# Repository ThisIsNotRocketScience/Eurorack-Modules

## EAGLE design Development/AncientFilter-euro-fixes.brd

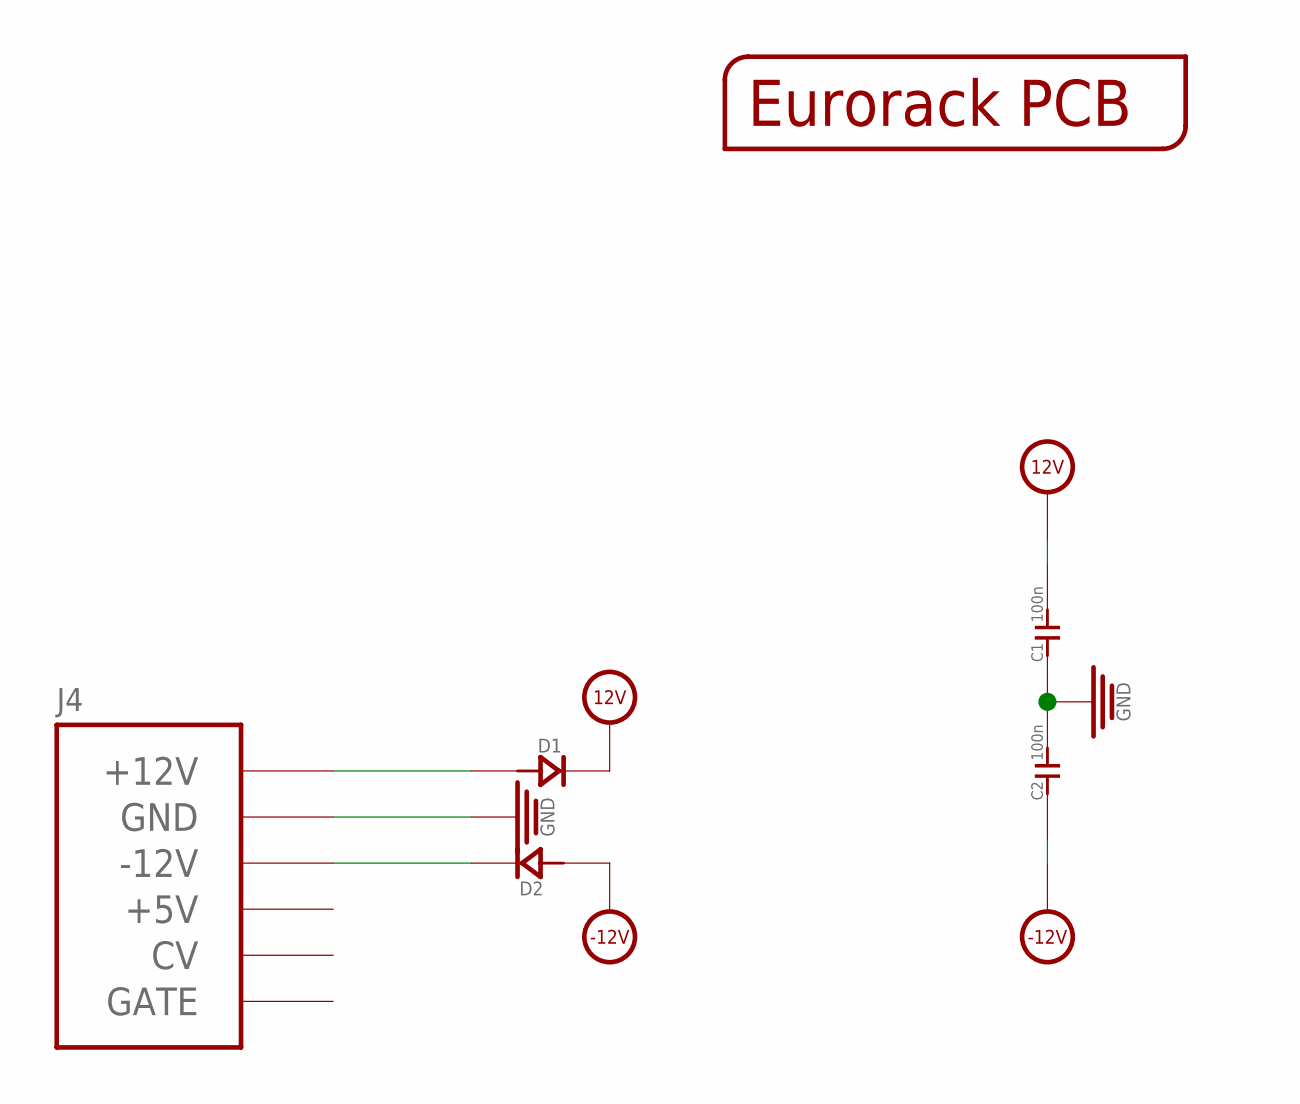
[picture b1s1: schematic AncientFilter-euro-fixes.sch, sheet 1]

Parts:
C1, C2: 100n; C0603
D1, D2: D-SMA; DO-214AC
J4: POWERSHROUDED; POWER_16_SHROUDED
PCB1: EURORACK_PCB12HP; EURORACK12HPPCB

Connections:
12V: C1.2, D1.2 (-); also elsewhere on the board
-12V: C2.1, D2.1 (+); also elsewhere on the board
GND: C1.1, C2.2, J4.3 (GND), J4.4 (GND), J4.5 (GND), J4.6 (GND), J4.7 (GND), J4.8 (GND); also elsewhere on the board
unnamed: D1.1 (+), J4.9 (+12V), J4.10 (+12V)
unnamed: D2.2 (-), J4.1 (-12V), J4.2 (-12V)

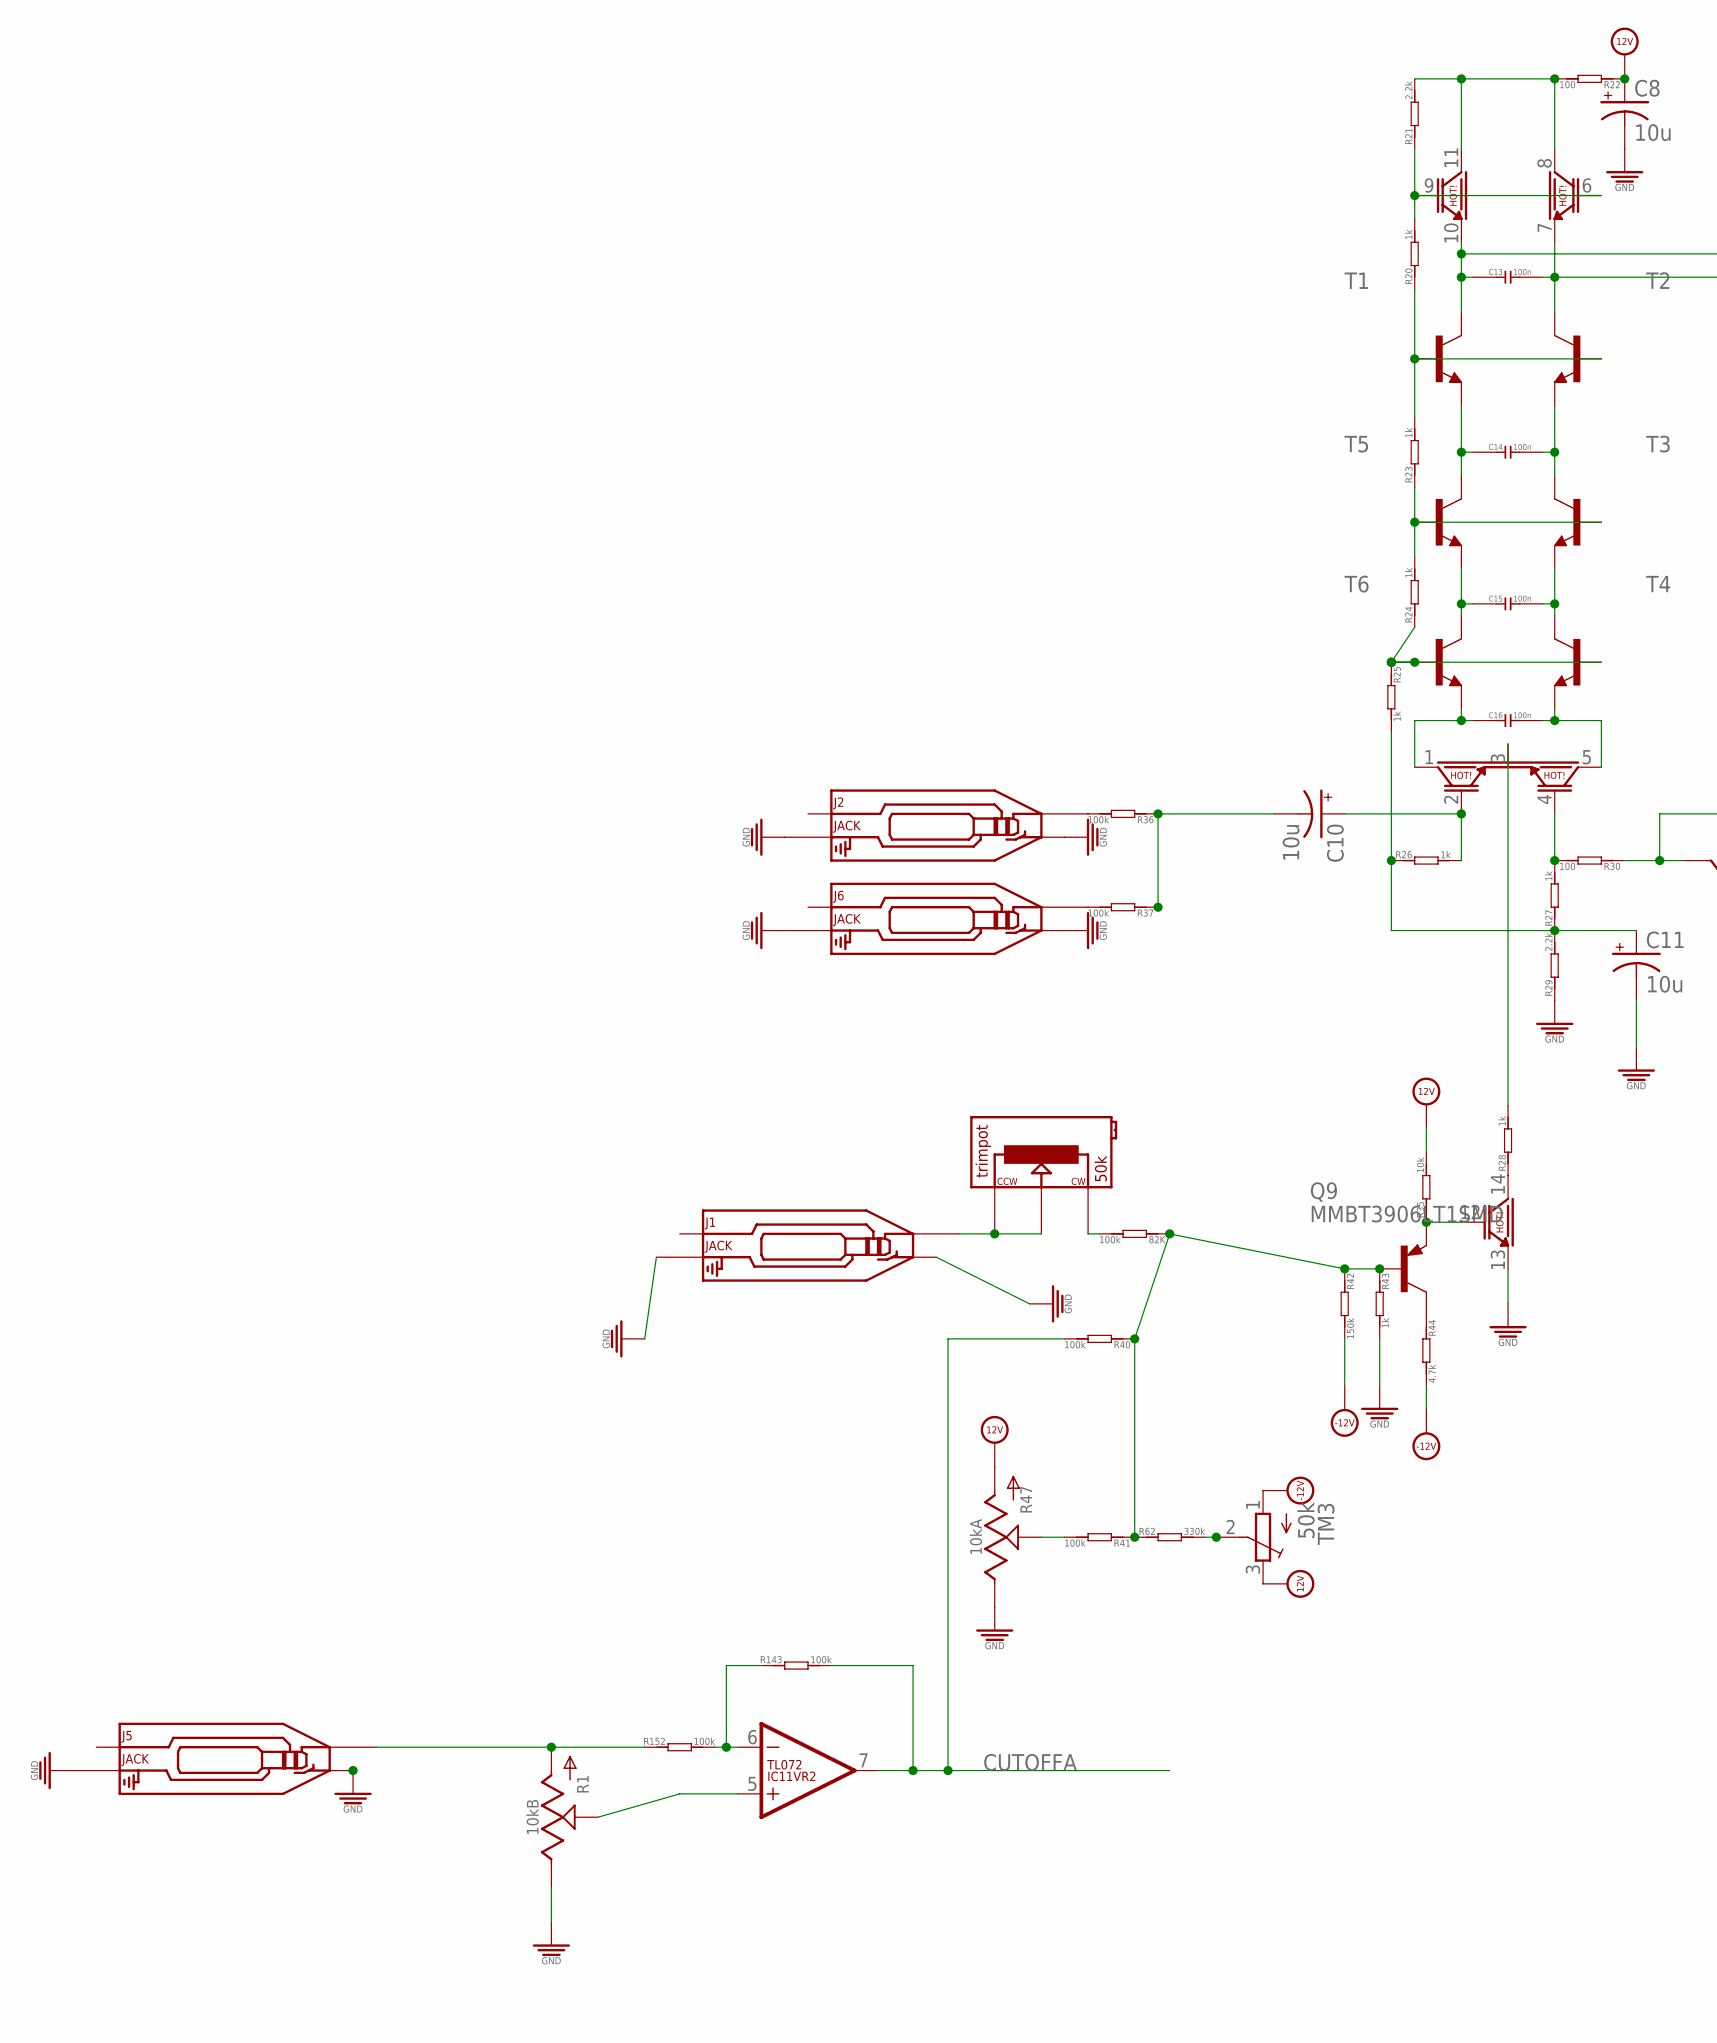
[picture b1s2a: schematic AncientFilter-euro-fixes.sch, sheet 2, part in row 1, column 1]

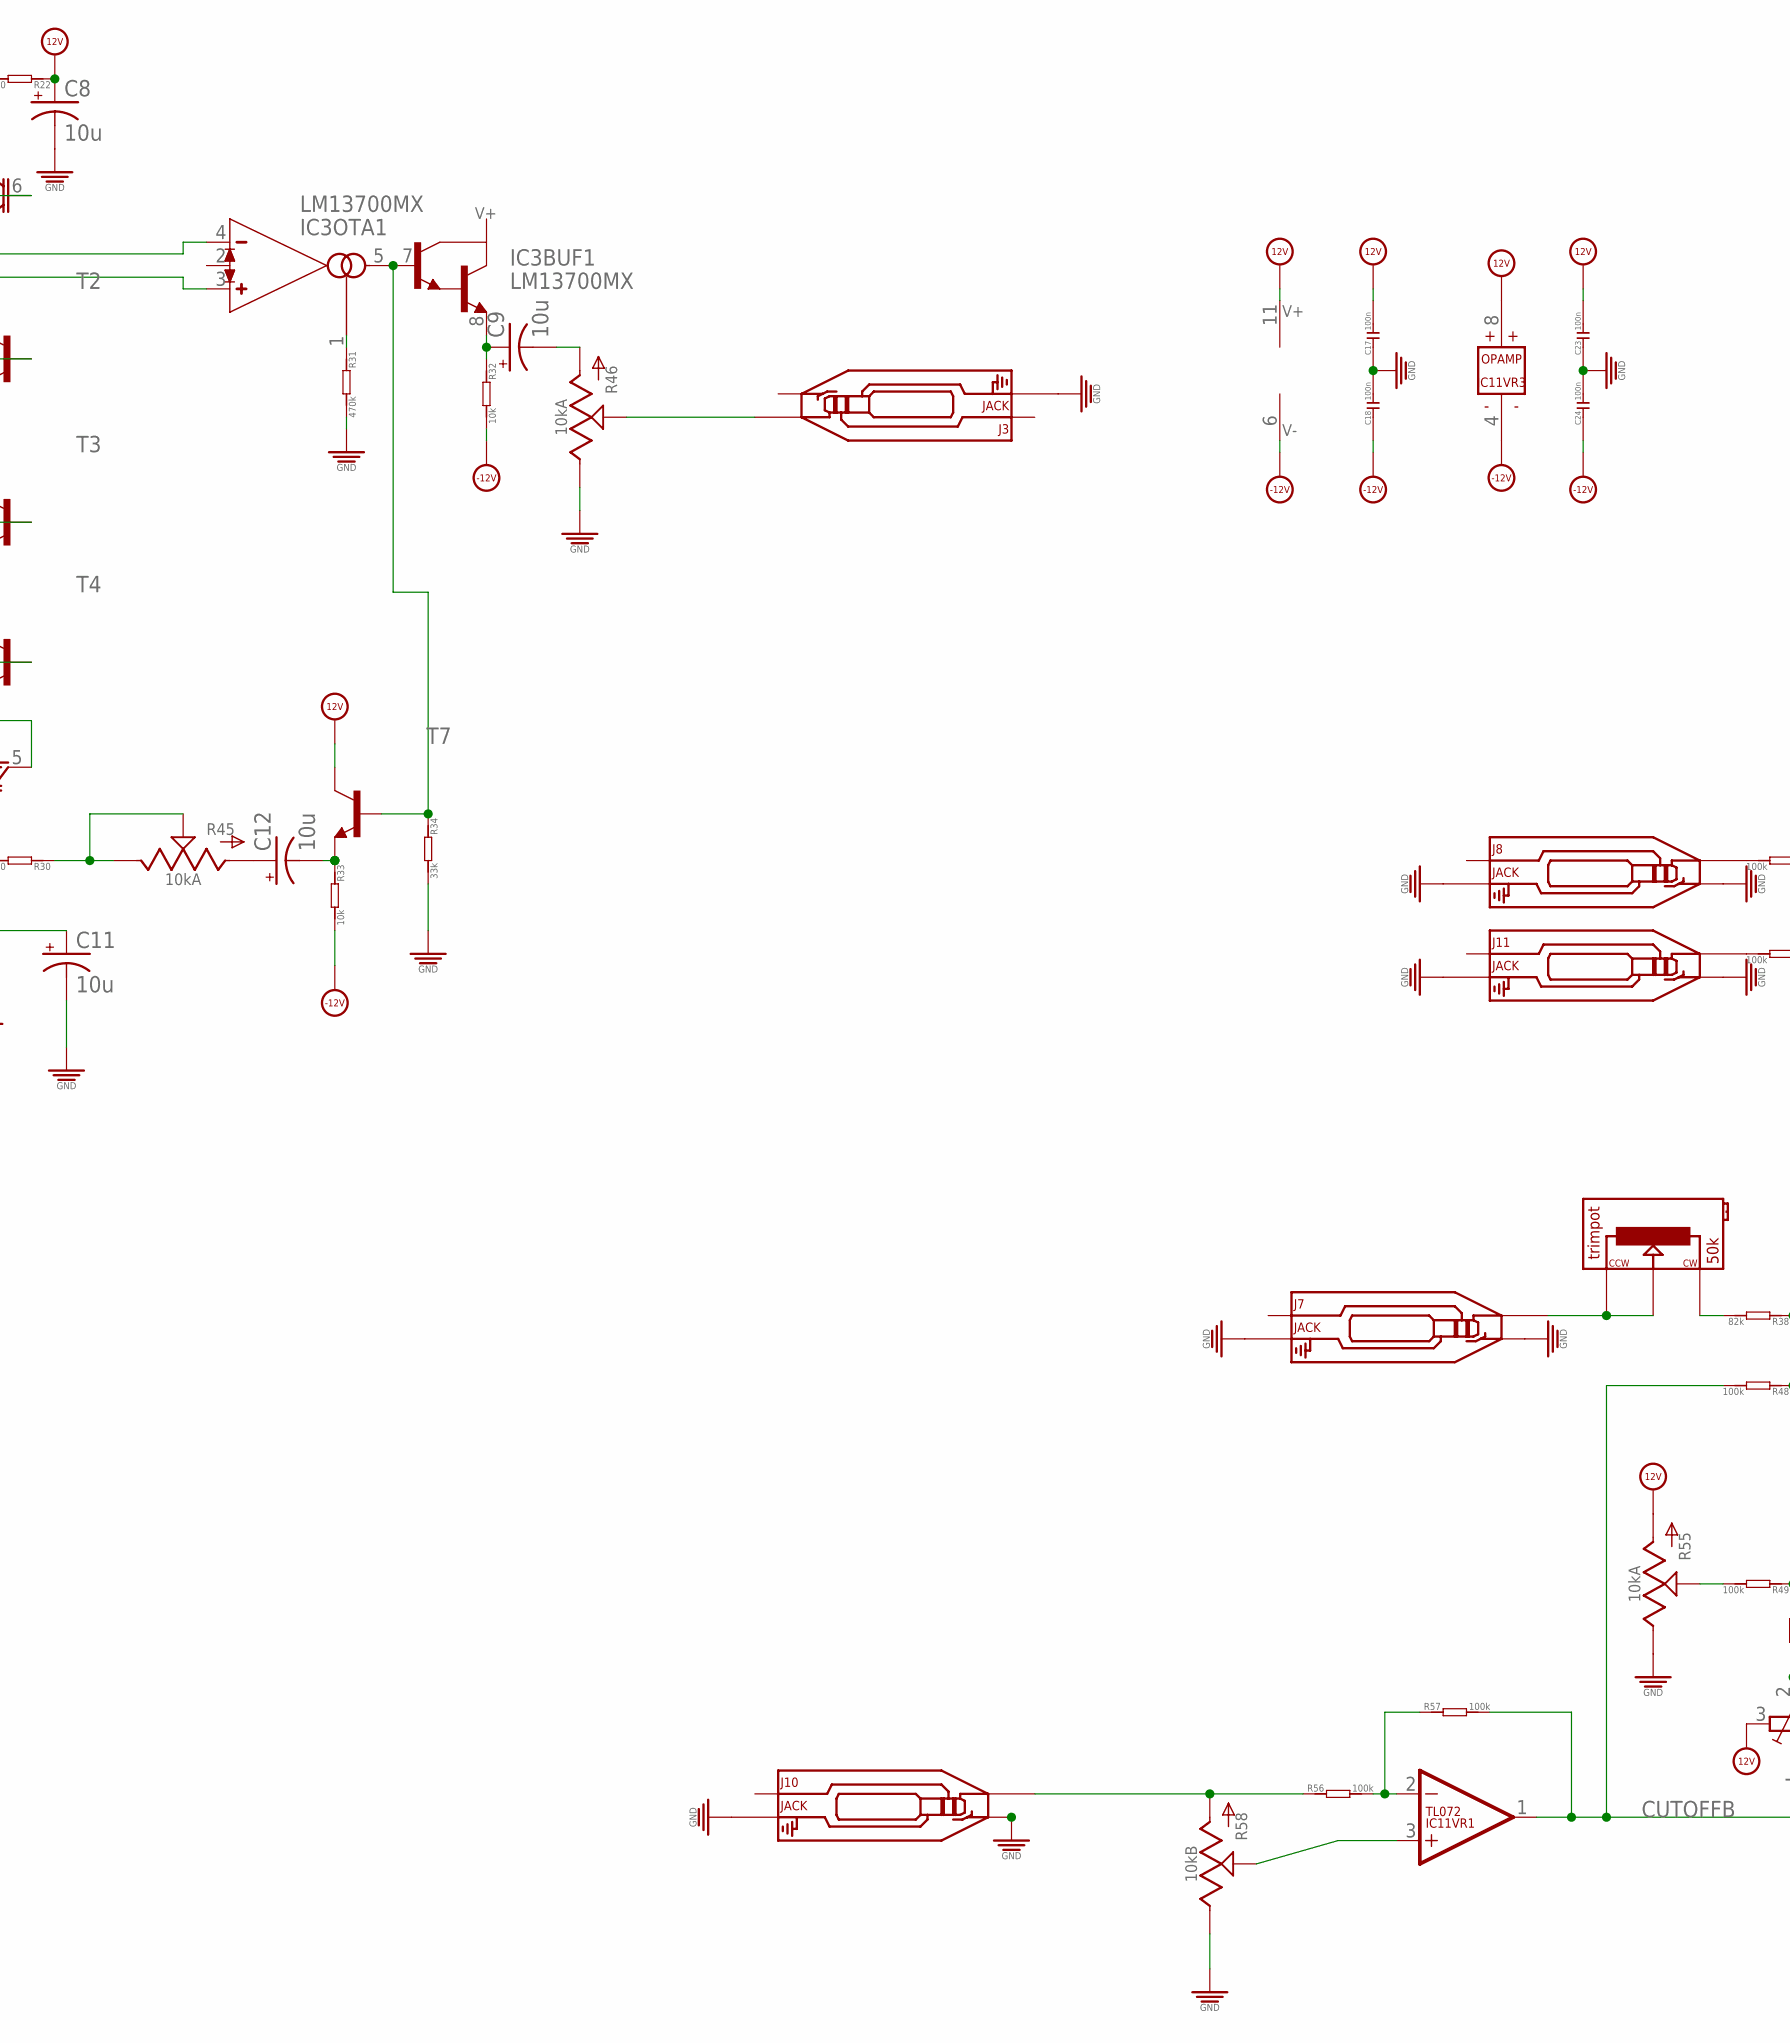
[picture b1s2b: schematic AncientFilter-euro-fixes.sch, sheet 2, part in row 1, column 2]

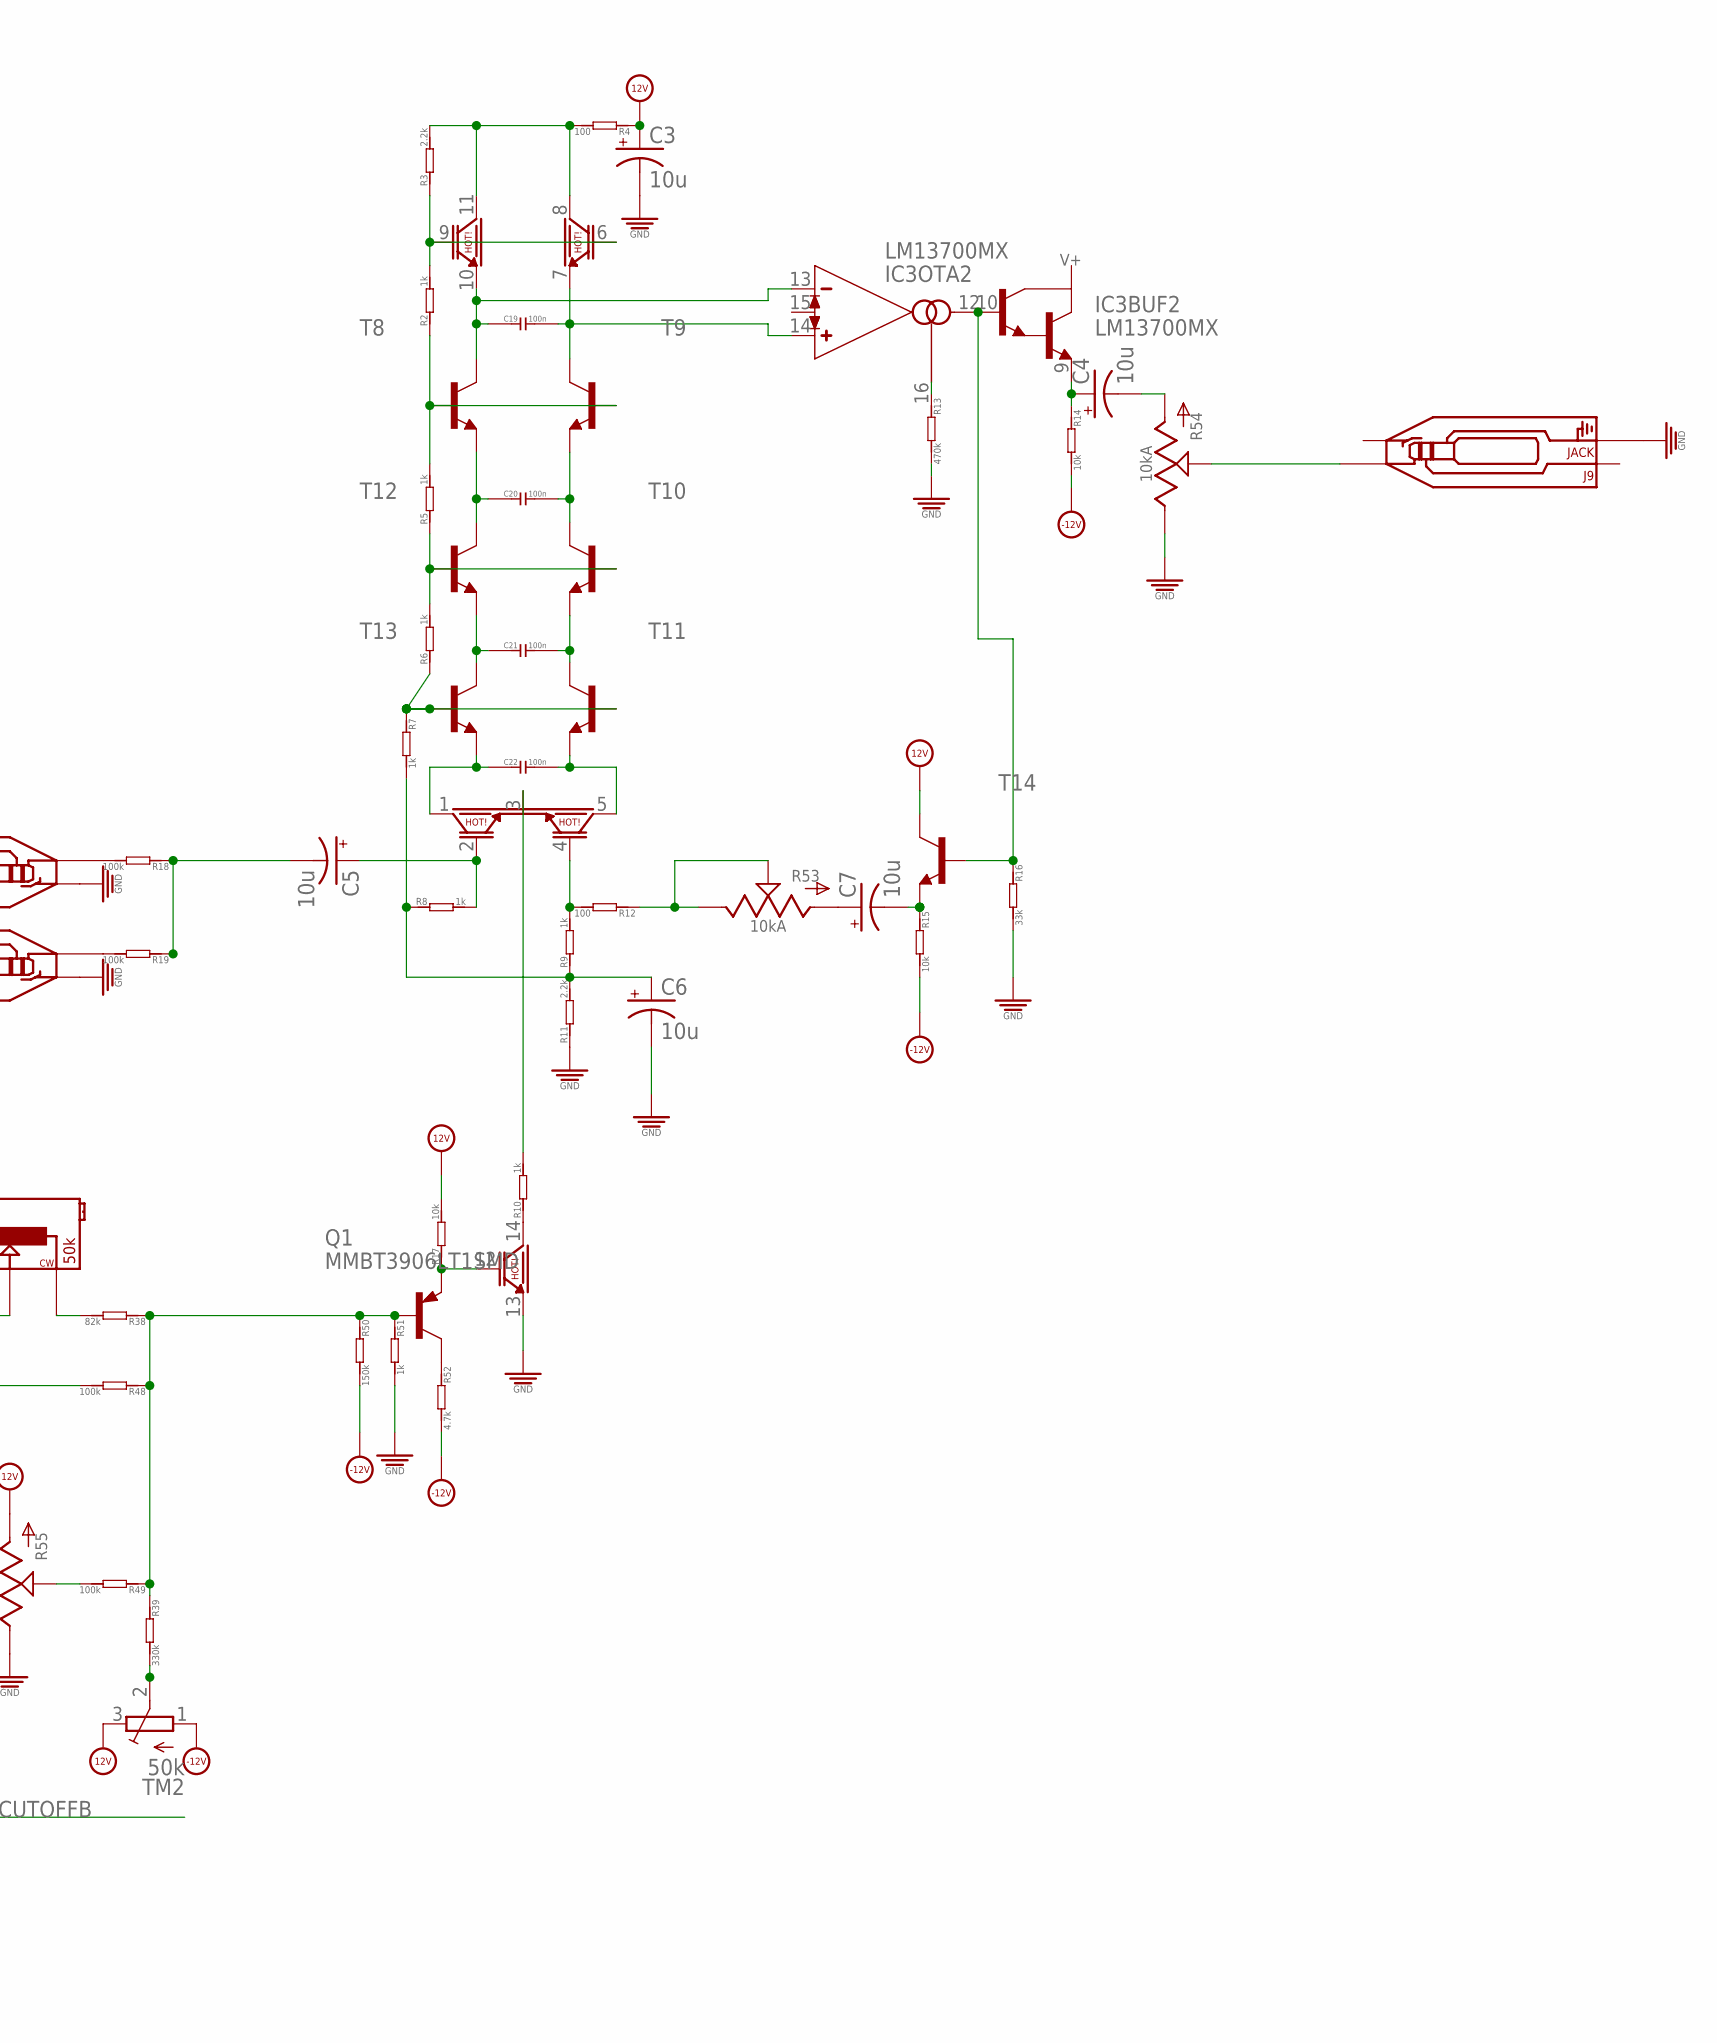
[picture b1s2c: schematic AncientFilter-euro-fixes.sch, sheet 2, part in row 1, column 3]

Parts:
82K: 100k; R0603
C3, C4, C5, C6, C7, C8, C9, C10, C11, C12: 10u; 153CLV-0605
C13, C14, C15, C16, C17, C18, C19, C20, C21, C22, C23, C24: 100n; C0603
IC3: LM13700MX; SO16
IC11: TL072; SO08
J1, J2, J3, J5, J6, J7, J8, J9, J10, J11: JACK; 3.5MM-JACK-SWITCH-13MM-NOHOLES
Q1, Q9: MMBT3906LT1SMD; SOT23-BEC
R1, R58: 10kB; ALPS_POT_SQUAREHOLES
R2, R5, R6, R7, R8, R9, R10, R20, R23, R24, R25, R26, R27, R28, R43, R51: 1k; R0603
R3, R11, R21, R29: 2.2k; R0603
R4, R12, R22, R30: 100; R0603
R13, R31: 470k; R0603
R14, R15, R17, R32, R33, R35: 10k; R0603
R16, R34: 33k; R0603
R18, R19, R36, R37, R40, R41, R48, R49, R56, R57, R143, R152: 100k; R0603
R38: 82k; R0603
R39, R62: 330k; R0603
R42, R50: 150k; R0603
R44, R52: 4.7k; R0603
R45, R46, R47, R53, R54, R55: 10kA; ALPS_POT_SQUAREHOLES
R61, R63: 50k; TRIMPOT
T1, T2, T3, T4, T5, T6, T7, T8, T9, T10, T11, T12, T13, T14: MMBT3904LT1-NPN-SOT23-BEC; SOT23-BEC
TM2, TM3: 50k; TC33X
U$1, U$2: LM3046; SO14

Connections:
12V: C3.+, C8.+, C17.2, C23.2, IC3.11 (V+), IC11.8 (V+), R4.1, R17.2, R22.1, R35.2, R47.P$3 (A), R55.P$3 (A), T7.C, T14.C, TM2.3 (E), TM3.3 (E); also elsewhere on the board
-12V: C18.1, C24.1, IC3.6 (V-), IC11.4 (V-), R14.2, R15.2, R32.2, R33.2, R42.2, R44.2, R50.2, R52.2, TM2.1 (A), TM3.1 (A); also elsewhere on the board
CUTOFF2_MODENVINPUT: J5.TIP_B@1 (TIP), J5.TIP_T@3 (TIP), R1.P$3 (A), R152.1
CUTOFF2_MODENVINPUT1: J10.TIP_B@1 (TIP), J10.TIP_T@3 (TIP), R56.1, R58.P$3 (A)
CUTOFFA: IC11.7 (OUT), R40.2, R143.2
CUTOFFB: IC11.1 (OUT), R48.2, R57.2
GND: C3.-, C6.-, C8.-, C11.-, C17.1, C18.2, C23.1, C24.2, J1.RING_B@1 (RING), J1.RING_T@3 (RING), J1.SWITCH_B@1 (SWITCH), J1.SWITCH_T@3 (SWITCH), J2.RING_B@1 (RING), J2.RING_T@3 (RING), J2.SWITCH_B@1 (SWITCH), J2.SWITCH_T@3 (SWITCH), J3.RING_B@1 (RING), J3.RING_T@3 (RING), J5.RING_B@1 (RING), J5.RING_T@3 (RING), J5.SWITCH_B@1 (SWITCH), J5.SWITCH_T@3 (SWITCH), J6.RING_B@1 (RING), J6.RING_T@3 (RING), J6.SWITCH_B@1 (SWITCH), J6.SWITCH_T@3 (SWITCH), J7.RING_B@1 (RING), J7.RING_T@3 (RING), J7.SWITCH_B@1 (SWITCH), J7.SWITCH_T@3 (SWITCH), J8.RING_B@1 (RING), J8.RING_T@3 (RING), J8.SWITCH_B@1 (SWITCH), J8.SWITCH_T@3 (SWITCH), J9.RING_B@1 (RING), J9.RING_T@3 (RING), J10.RING_B@1 (RING), J10.RING_T@3 (RING), J10.SWITCH_B@1 (SWITCH), J10.SWITCH_T@3 (SWITCH), J11.RING_B@1 (RING), J11.RING_T@3 (RING), J11.SWITCH_B@1 (SWITCH), J11.SWITCH_T@3 (SWITCH), R1.P$1 (E), R11.1, R13.2, R16.2, R29.1, R31.2, R34.2, R43.2, R46.P$1 (E), R47.P$1 (E), R51.2, R54.P$1 (E), R55.P$1 (E), R58.P$1 (E), U$1.13 (E), U$2.13 (E); also elsewhere on the board
unnamed: Q9.E, R35.1, U$2.12 (B)
unnamed: J6.TIP_B@1 (TIP), J6.TIP_T@3 (TIP), R37.2
unnamed: Q1.E, R17.1, U$1.12 (B)
unnamed: C7.-, R15.1, T14.E
unnamed: R49.2, R55.P$2 (S)
unnamed: R2.2, R3.1, U$1.6 (B), U$1.9 (B)
unnamed: C19.1, IC3.13 (IN_N), T8.C, U$1.10 (E)
unnamed: C19.2, IC3.14 (IN_P), T9.C, U$1.7 (E)
unnamed: C20.1, T8.E, T12.C
unnamed: C20.2, T9.E, T10.C
unnamed: C21.1, T12.E, T13.C
unnamed: C21.2, T10.E, T11.C
unnamed: C22.2, T11.E, U$1.5 (C1)
unnamed: C22.1, T13.E, U$1.1 (C2)
unnamed: C12.-, R33.1, T7.E
unnamed: R2.1, R5.2, T8.B, T9.B
unnamed: R5.1, R6.2, T10.B, T12.B
unnamed: R6.1, R7.1, T11.B, T13.B
unnamed: R10.2, U$1.3 (E)
unnamed: R10.1, U$1.14 (C)
unnamed: Q1.C, R52.1
unnamed: Q1.B, R38.1, R39.1, R48.1, R49.1, R50.1, R51.1
unnamed: C5.+, R8.2, U$1.2 (B2)
unnamed: R41.2, R47.P$2 (S)
unnamed: R20.2, R21.1, U$2.6 (B), U$2.9 (B)
unnamed: C13.1, IC3.4 (IN_N), T1.C, U$2.10 (E)
unnamed: C13.2, IC3.3 (IN_P), T2.C, U$2.7 (E)
unnamed: C14.1, T1.E, T5.C
unnamed: C14.2, T2.E, T3.C
unnamed: C15.1, T5.E, T6.C
unnamed: C15.2, T3.E, T4.C
unnamed: C16.2, T4.E, U$2.5 (C1)
unnamed: C16.1, T6.E, U$2.1 (C2)
unnamed: R20.1, R23.2, T1.B, T2.B
unnamed: R23.1, R24.2, T3.B, T5.B
unnamed: R24.1, R25.1, T4.B, T6.B
unnamed: C10.+, R26.2, U$2.2 (B2)
unnamed: R28.2, U$2.3 (E)
unnamed: R28.1, U$2.14 (C)
unnamed: Q9.C, R44.1
unnamed: 82K.1, Q9.B, R40.1, R41.1, R42.1, R43.1, R62.1
unnamed: C10.-, R36.1, R37.1
unnamed: C11.+, R25.2, R26.1, R27.1, R29.2
unnamed: R27.2, R30.2, U$2.4 (B1)
unnamed: R21.2, R22.2, U$2.8 (C), U$2.11 (C)
unnamed: C5.-, R18.1, R19.1
unnamed: IC3.1 (I_BIAS), R31.1
unnamed: C9.-, R46.P$3 (A)
unnamed: IC3.5 (OUT), IC3.7 (B), R34.1, T7.B
unnamed: C9.+, IC3.8 (E), R32.1
unnamed: J3.TIP_B@1 (TIP), J3.TIP_T@3 (TIP), R46.P$2 (S)
unnamed: R30.1, R45.P$1 (E), R45.P$2 (S)
unnamed: C12.+, R45.P$3 (A)
unnamed: J1.TIP_B@1 (TIP), J1.TIP_T@3 (TIP), R61.P$1, R61.P$2
unnamed: J2.TIP_B@1 (TIP), J2.TIP_T@3 (TIP), R36.2
unnamed: C6.+, R7.2, R8.1, R9.1, R11.2
unnamed: R9.2, R12.2, U$1.4 (B1)
unnamed: R3.2, R4.2, U$1.8 (C), U$1.11 (C)
unnamed: IC3.16 (I_BIAS), R13.1
unnamed: C4.-, R54.P$3 (A)
unnamed: IC3.10 (B), IC3.12 (OUT), R16.1, T14.B
unnamed: C4.+, IC3.9 (E), R14.1
unnamed: J9.TIP_B@1 (TIP), J9.TIP_T@3 (TIP), R54.P$2 (S)
unnamed: R12.1, R53.P$1 (E), R53.P$2 (S)
unnamed: C7.+, R53.P$3 (A)
unnamed: J7.TIP_B@1 (TIP), J7.TIP_T@3 (TIP), R63.P$1, R63.P$2
unnamed: J8.TIP_B@1 (TIP), J8.TIP_T@3 (TIP), R18.2
unnamed: IC11.2 (-IN), R56.2, R57.1
unnamed: IC11.3 (+IN), R58.P$2 (S)
unnamed: J11.TIP_B@1 (TIP), J11.TIP_T@3 (TIP), R19.2
unnamed: 82K.2, R61.P$3
unnamed: R39.2, TM2.2 (S)
unnamed: R62.2, TM3.2 (S)
unnamed: R38.2, R63.P$3
unnamed: IC11.6 (-IN), R143.1, R152.2
unnamed: IC11.5 (+IN), R1.P$2 (S)

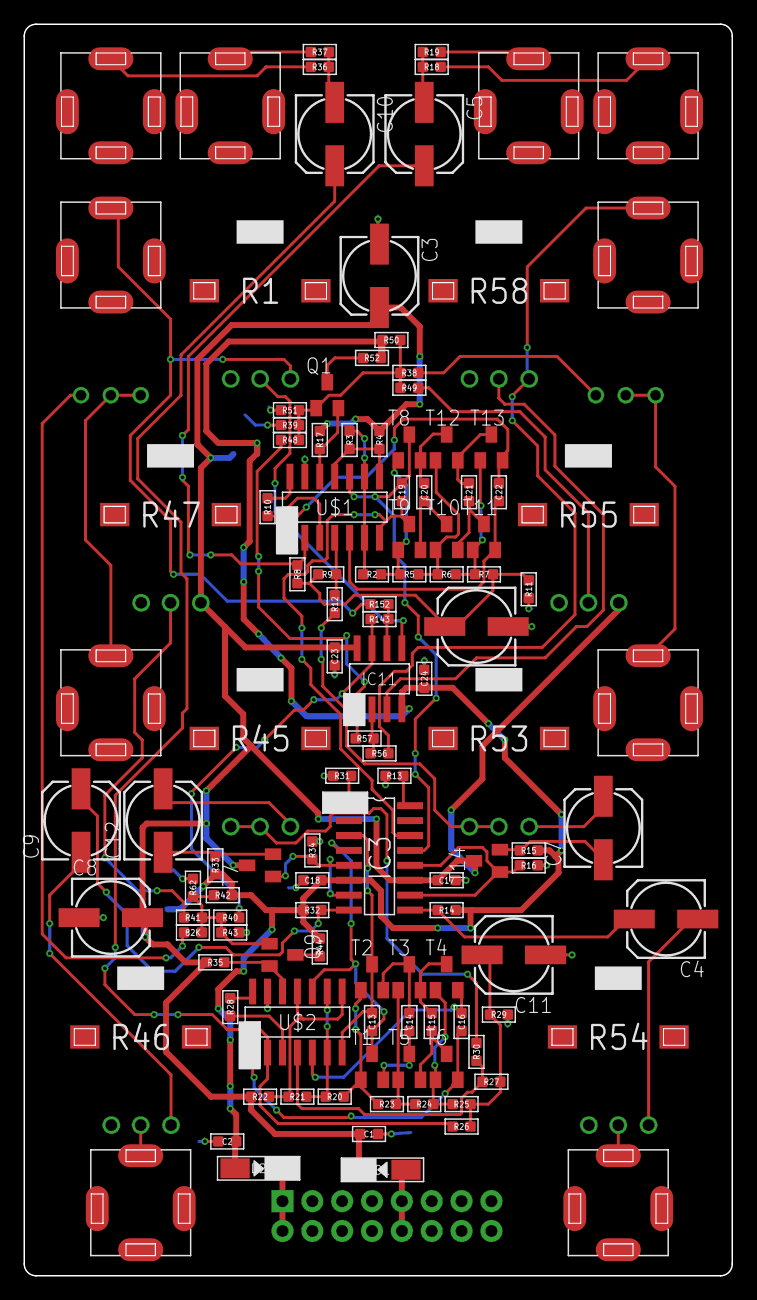
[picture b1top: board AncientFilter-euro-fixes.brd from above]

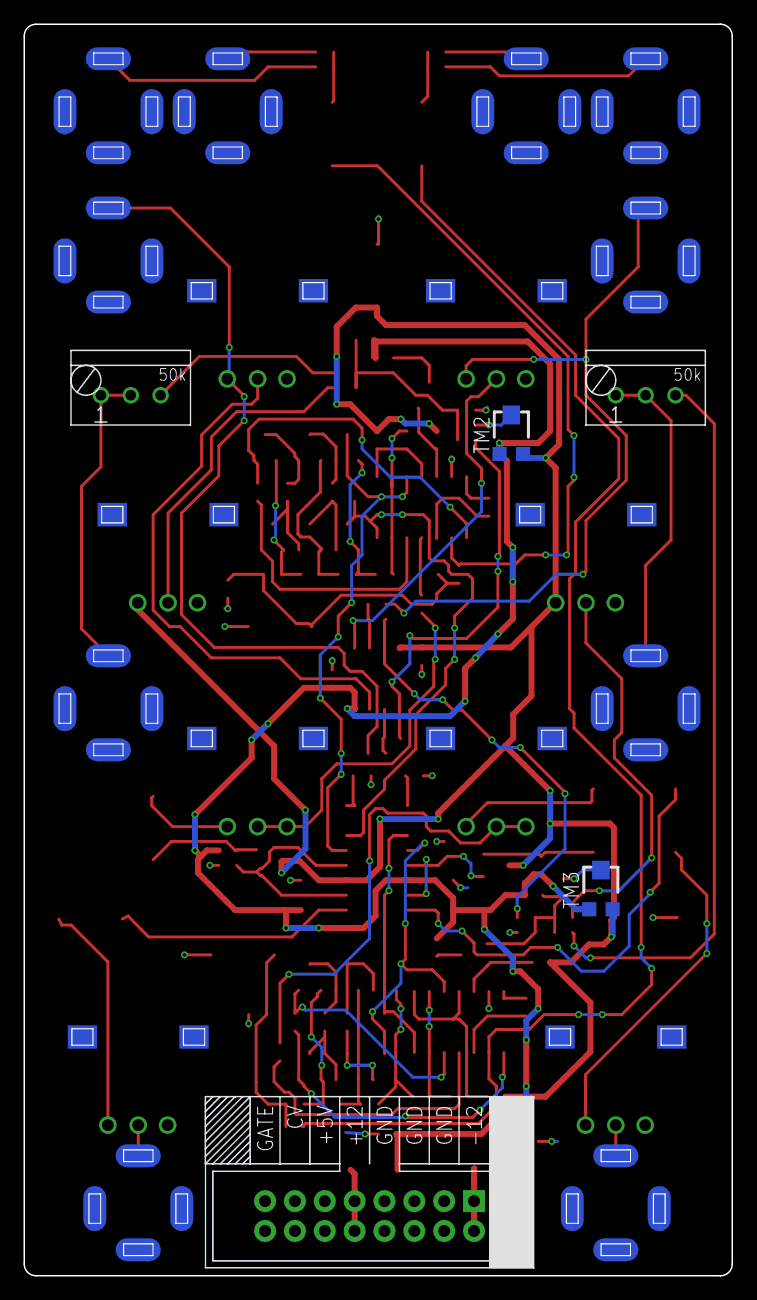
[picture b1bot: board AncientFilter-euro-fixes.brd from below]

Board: 2 copper layers, 60.2 x 106.5 mm, 124 parts (5 on the bottom side), 85 nets.

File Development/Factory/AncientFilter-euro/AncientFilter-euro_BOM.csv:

Comment,Designator,Footprint,LCSC Part #,combinedname,name
LM3046,"U$2, U$1",SO14,,LM3046_SO14_LM3046,LM3046
,"T1, T2, T3, T4, T5, T6, T7, T8, T9, T10, T11, T12, T13, T14",SOT23-BEC,,*-NPN-_SOT23-BEC_,*-NPN-
MMBT3906LT1SMD,"Q9, Q1",SOT23-BEC,,MMBT3906*_SOT23-BEC_MMBT3906LT1SMD,MMBT3906*
LM13700MX,"IC3",SO16,,LM13700_SO16_LM13700MX,LM13700
1k,"R20, R23, R24, R25, R26, R27, R28, R43, R2, R5, R6, R7, R8, R9, R10, R51",R0603,,R*_R0603_1k,R*
2.2k,"R21, R29, R3, R11",R0603,,R*_R0603_2.2k,R*
100,"R22, R30, R4, R12",R0603,,R*_R0603_100,R*
470k,"R31, R13",R0603,,R*_R0603_470k,R*
10k,"R32, R33, R35, R14, R15, R17",R0603,,R*_R0603_10k,R*
33k,"R34, R16",R0603,,R*_R0603_33k,R*
100k,"R36, R37, 82K, R40, R41, R152, R143, R18, R19, R48, R49, R56, R57",R0603,,R*_R0603_100k,R*
150k,"R42, R50",R0603,,R*_R0603_150k,R*
4.7k,"R44, R52",R0603,,R*_R0603_4.7k,R*
82k,"R38",R0603,,R*_R0603_82k,R*
330k,"R39, R62",R0603,,R*_R0603_330k,R*
10u,"C8, C9, C10, C11, C12, C3, C4, C5, C6, C7",153CLV-0605,,CPOL-US_153CLV-0605_10u,CPOL-US
100n,"C13, C14, C15, C16, C17, C18, C1, C2, C19, C20, C21, C22, C23, C24",C0603,,C*_C0603_100n,C*
10kA,"R45, R46, R47, R53, R54, R55",ALPS_POT_SQUAREHOLES,,POT_ALPS_POT_SQUAREHOLES_10kA,POT
10kB,"R1, R58",ALPS_POT_SQUAREHOLES,,POT_ALPS_POT_SQUAREHOLES_10kB,POT
JACK,"J1, J2, J3, J5, J6, J7, J8, J9, J10, J11",3.5MM-JACK-SWITCH-13MM-NOHOLES,,AUDIO-JACK_SMALLSYMBOL_3.5MM-JACK-SWITCH-13MM-NOHOLES_JACK,AUDIO-JACK_SMALLSYMBOL
EURORACK_PCB12HP,"PCB1",EURORACK12HPPCB,,EURORACK_PCB_EURORACK12HPPCB_EURORACK_PCB12HP,EURORACK_PCB
,"D1, D2",DO-214AC,,D*_DO-214AC_,D*
POWERSHROUDED,"J4",POWER_16_SHROUDED,,POWER_POWER_16_SHROUDED_POWERSHROUDED,POWER
TL072,"IC11",SO08,,TL072_SO08_TL072,TL072
50k,"R61, R63",TRIMPOT,,TRIMPOT_TRIMPOT_50k,TRIMPOT
50k,"TM2, TM3",TC33X,,TRIMPOT_TC33X_50k,TRIMPOT

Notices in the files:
parts and their libraries:
SparkFun-Aesthetics: Licensing: CC v3.0 Share-Alike You are welcome to use this library for commercial purposes.
